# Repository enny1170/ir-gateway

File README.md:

# Introduction 
This is a fork of the famous [ESP8266-RcOid](https://www.rcoid.de/ESP8266.html) Project

the Hardware is changed to a Wemos D1 mini pro alternativly Wemos D1 32 (pincompatible) and the is software updated to support this.
And a custom Board are developed. To easy hookup this on the Module.
Most parts are rewritten, because I want to use this also as IR-Gateway togeter with my Smart-Home.
So we change to ESP Async-Webser and AsyncMQTT. Adding a better WebUI to support Storage and Management of Codes via Web-Ui.

To have a good Support for multiple Clients at the same Device we have designet to work without any blocking functions.
All API's needed to support the Rcoid-App exist. So the App is fully suported.

This project contains also several shematics.
1. a circurit and a pcb to simply Hookup on the given Module. (shematics/kicad/) [IR-Shield](https://www.pcbway.com/project/shareproject/IR_Shield_for_wemos_D1_pro_or_Wemos_D1_32.html)
2. 3D printable STL-Files as for a Cover (shematic/3dprint)
3. a Freecad Project to build or modify the Case (shematic/freecad)

# Usage (extract from Device Readme)
    This Firmware is a complete new Implementation of the [Rcoid](https://rcoid.de/) Project.
    This implementation supports the same Interface for the RcOid App. Has a extended Web UI and REST-Api. Devices can be used as IR-Gateway trought MQTT. 

    Sending and reciving IR-Codes new implemented for blocking free work. Also the storage of IR-Codes (Commands) added. This Commands can be used for MQTT and REST. 
    Upload and Downlowad of stored commands are possible. 

    A new unconfigured Device will start in Accesspoint-Mode and provide a 'ESP8266 for RCoid Access Point' with Password passpass on IP 192.168.0.1. 
    You are able to setup SSID and Password for your local WiFi-Connection.
    From the Root-Page you have also the possibility tor reboot, remove Web Config, and reset to Factory.
    Only from this page you can enable IR-reciving to capture IR-Codes.
    From the MQTT Page you can ste the Connection to your MQTT-Server and a Prefix used for the topic on MQTT. If the MQTT-Server adress empty or a '.' the MQTT communication will be disabled.
    In MQTT-Broker the device will be provide its local IP-Adress and available commands. The device subscribes /[Prefix]/Cmd. If the device receive a String in this topic, this will be interpreted as a Command. 
    The device try to find this Command and will send the Code immedaly.
    The same Functionality can be reached by sending a GET-Request to /cmd?button=xxxx. Where xxxx the name of the command. It can be taken from the Command-Page.

    The Command page are selfexplanating. But two points you have to know. Editing a Command you have to set a Code and a Name. The Name will be used as Filename to store the command on device Flash.
    And also as Command to raise from MQTT. The Clock Icon on the Command-Page will give you the possibilty to setup one Timer to send this command later.

    Some devices needs to receive a Code multiple times. So we add a Option Repeat for stored Commands. This will repeat the IR-Output according to this setting. Minimum is 1 maximum 5.

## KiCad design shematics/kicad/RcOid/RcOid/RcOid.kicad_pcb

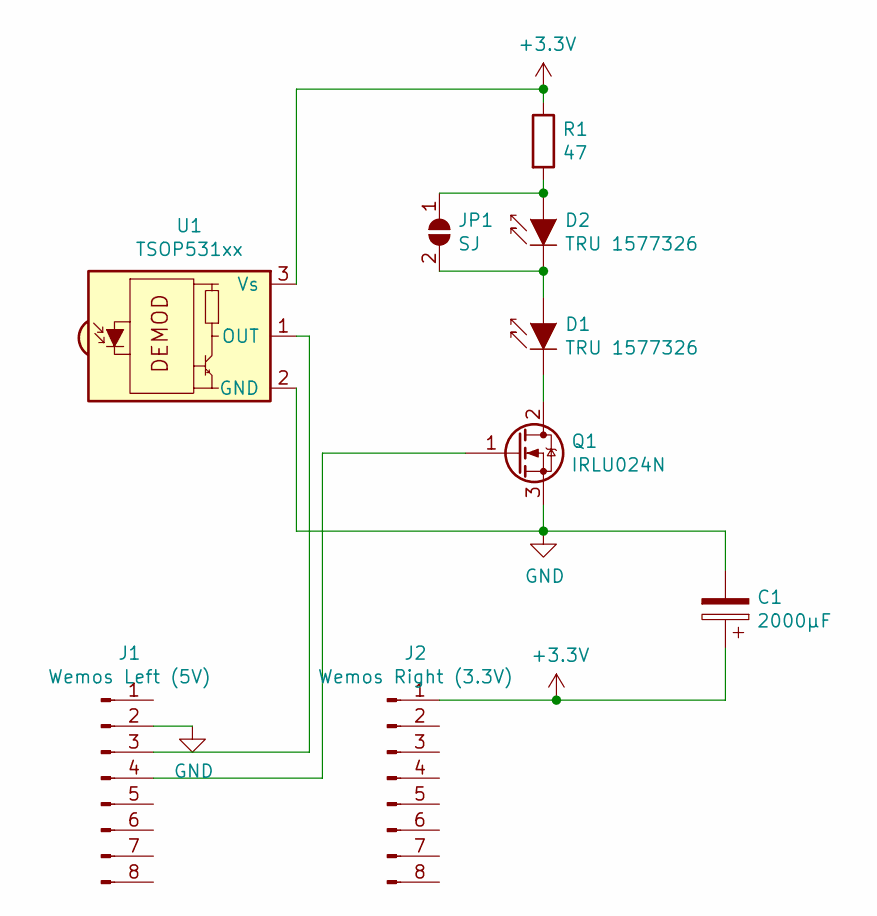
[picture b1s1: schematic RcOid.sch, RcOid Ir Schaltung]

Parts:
C1: 2000µF; CP_Radial_D10.0mm_P2.50mm
D1: TRU 1577326; LED_D5.0mm_Horizontal_O1.27mm_Z3.0mm_IRGrey
D2: TRU 1577326; LED_D5.0mm_IRGrey
J1: Wemos Left (5V); PinHeader_1x08_P2.54mm_Vertical
J2: Wemos Right (3.3V); PinHeader_1x08_P2.54mm_Vertical
JP1: SJ; SolderJumper-2_P1.3mm_Open_Pad1.0x1.5mm
Q1: IRLU024N; TO-251-2-1EP_Horizontal_TabDown
R1: 47; R_Axial_DIN0411_L9.9mm_D3.6mm_P15.24mm_Horizontal
U1: TSOP531xx; Vishay_MINIMOLD-3Pin

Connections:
+3V3: C1.1, J2.1, R1.1, U1.3 (Vs)
GND: C1.2, J1.2, Q1.3 (S), U1.2 (GND)
unnamed: D1.1 (K), Q1.2 (D)
unnamed: D1.2 (A), D2.1 (K), JP1.2 (B)
unnamed: D2.2 (A), JP1.1 (A), R1.2
unnamed: J1.3, U1.1 (OUT)
unnamed: J1.4, Q1.1 (G)

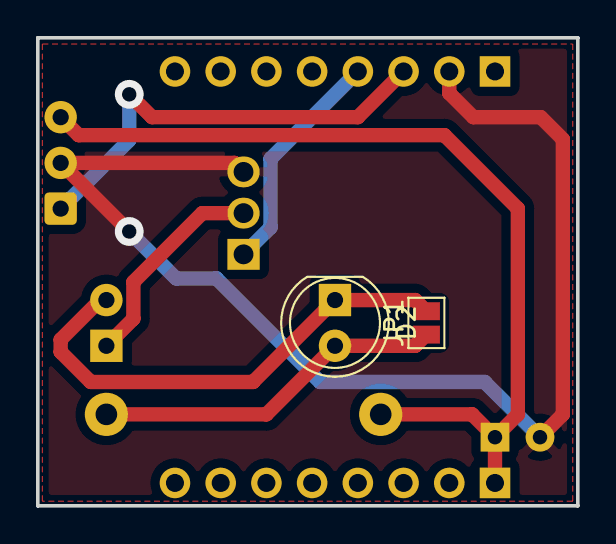
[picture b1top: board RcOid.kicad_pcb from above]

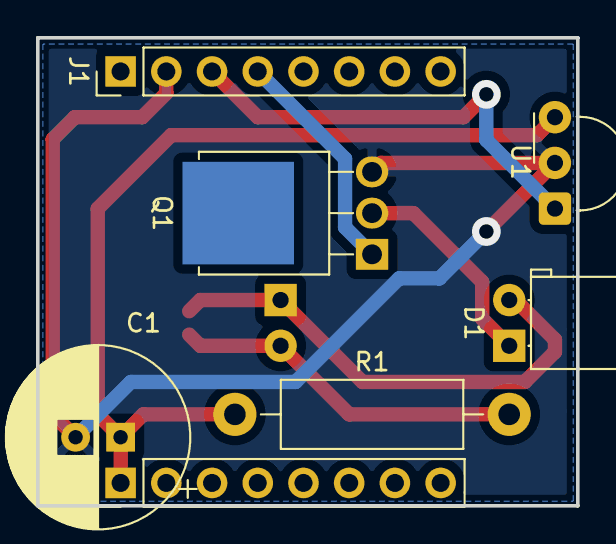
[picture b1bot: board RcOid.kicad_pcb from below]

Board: 2 copper layers, 30.0 x 26.0 mm, 9 parts (7 on the bottom side), 7 nets.

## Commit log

2020-11-08 Added README.md
2020-11-08 first checkin
2020-11-08 Schematc Update
2020-11-08 change R
2020-11-08 Case V1
2020-11-08 AP Seite angepasst
2020-11-09 code aufgeräumt Web Gui Schick
2020-11-09 fix menu
2020-11-10 TH PCB
2020-11-29 mqtt drin compiliert
2020-11-29 laden Mqqt fürhrt zu restart
2020-11-30 reset casue 4 ka warum
2020-12-01 Start Umab auf Async
2020-12-01 change pcb layout
2020-12-02 Webseiten auf Async Webserver umgebaut, Serverinit
2020-12-03 fix solder Mask
2020-12-03 add esp32 Build
2020-12-03 fix Build errors after env change
2020-12-04 mqtt topic vergleich tut nicht
2020-12-04 ESP32 läuft 8266 reboot 4
2020-12-07 fix PCB wrong Footprint
2020-12-13 V2 Mechanics
2020-12-13 fix ircommand page
2020-12-18 IR handling auf Asyncron umgebaut
2020-12-19 Ir Receive geht nun, cmdPage überarbeitet
2020-12-20 fix edit Cmd
2020-12-20 Deleted config.json
2020-12-20 config wieder hinzu gefügt
2020-12-20 download for Cmd implemented
2020-12-20 Upload mit mehreren Files möglich
2020-12-21 implemented fix Rcoid also
2020-12-22 ESP32 is running on this code
2020-12-24 Added Wemos_D1_mini32 pincompatible 2 D1 min
2020-12-28 Basicly working on both systems
2020-12-28 fix receiver
2020-12-29 Werte aktualisiert
2021-01-06 add gccode
2021-01-06 add new Field in WebUi
2021-01-09 finish Timer and Readme
2021-01-11 Camand Page auf chunked umgebaut
2021-01-11 debug code entfernt
2021-01-11 add repeat Option
2021-01-11 Add OTA
2021-01-11 readme
2021-01-11 1 checkin
2021-01-11 confg examples
2021-01-11 ready for publish on Github
2021-01-11 ready for publish
2021-01-11 remove heap infos
2021-01-11 Fix send Command from Webpage
2021-01-11 fix Cmd from WebUi
2021-01-12 fix IrReceive WebUi
2021-01-13 add webupdater
2021-01-13 Fix for Irreceive and Webupdate
2021-01-13 Change Versioning to ini and Filnames for firmewa
2021-01-13 gitignore
